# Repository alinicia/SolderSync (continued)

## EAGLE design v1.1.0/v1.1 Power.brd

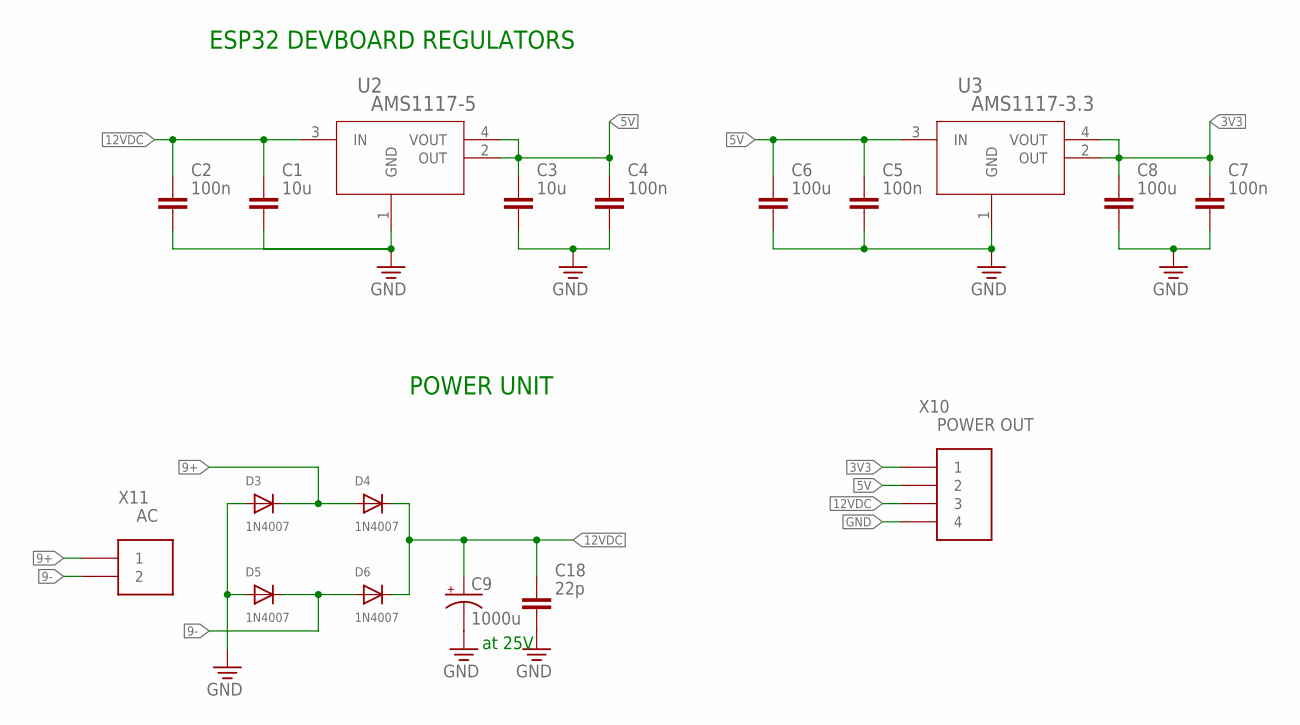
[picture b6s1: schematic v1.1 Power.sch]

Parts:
C1, C3: 10u; CAPC2012X110
C2, C4, C5, C7: 100n; CAPC2012X110
C6, C8: 100u; CAPC2012X110
C9: 1000u; CAP_10X20IN
C18: 22p; CAPC2012X110
D3, D4, D5, D6: 1N4007; SOD-123FL
U2: AMS1117-5; _AMS-L
U3: AMS1117-3.3; _ADS-L
X10: POWER OUT; JST-XH-04-PACKAGE-LONG-PAD
X11: AC; -LONG-PAD

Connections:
3V3: C7.1, C8.1, U3.2 (OUT), U3.4 (VOUT), X10.1
5V: C3.1, C4.1, C5.1, C6.1, U2.2 (OUT), U2.4 (VOUT), U3.3 (IN), X10.2
9+: D3.C, D4.A, X11.1
9-: D5.C, D6.A, X11.2
12VDC: C1.1, C2.1, C9.1 (+), C18.1, D4.C, D6.C, U2.3 (IN), X10.3
GND: C1.2, C2.2, C3.2, C4.2, C5.2, C6.2, C7.2, C8.2, C9.2 (-), C18.2, D3.A, D5.A, U2.1 (GND), U3.1 (GND), X10.4

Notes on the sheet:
ESP32 DEVBOARD REGULATORS
POWER UNIT
at 25V

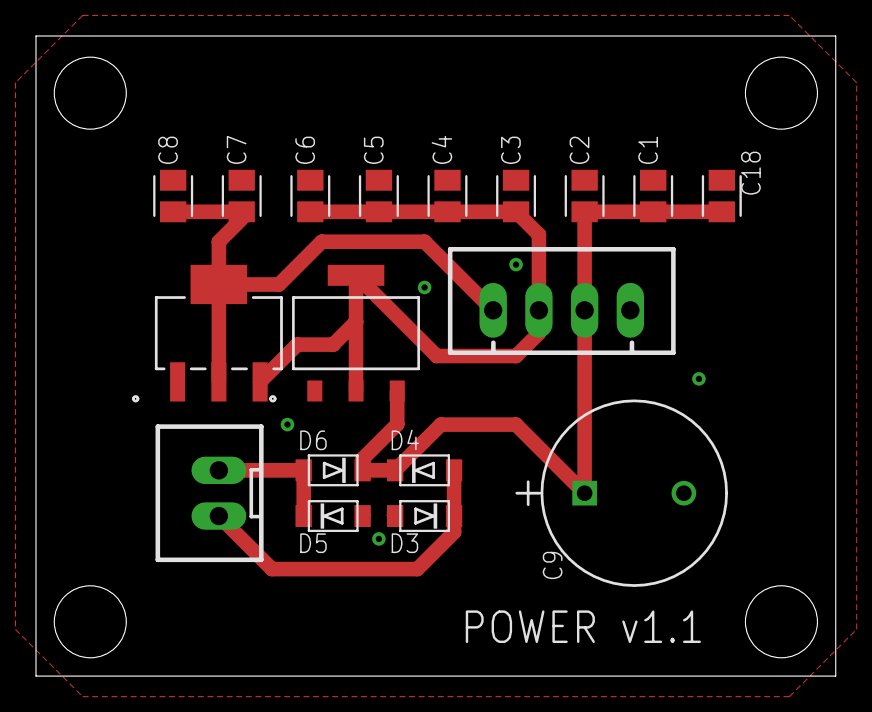
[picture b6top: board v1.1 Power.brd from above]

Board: 2 copper layers, 44.4 x 35.6 mm, 18 parts (0 on the bottom side), 6 nets.

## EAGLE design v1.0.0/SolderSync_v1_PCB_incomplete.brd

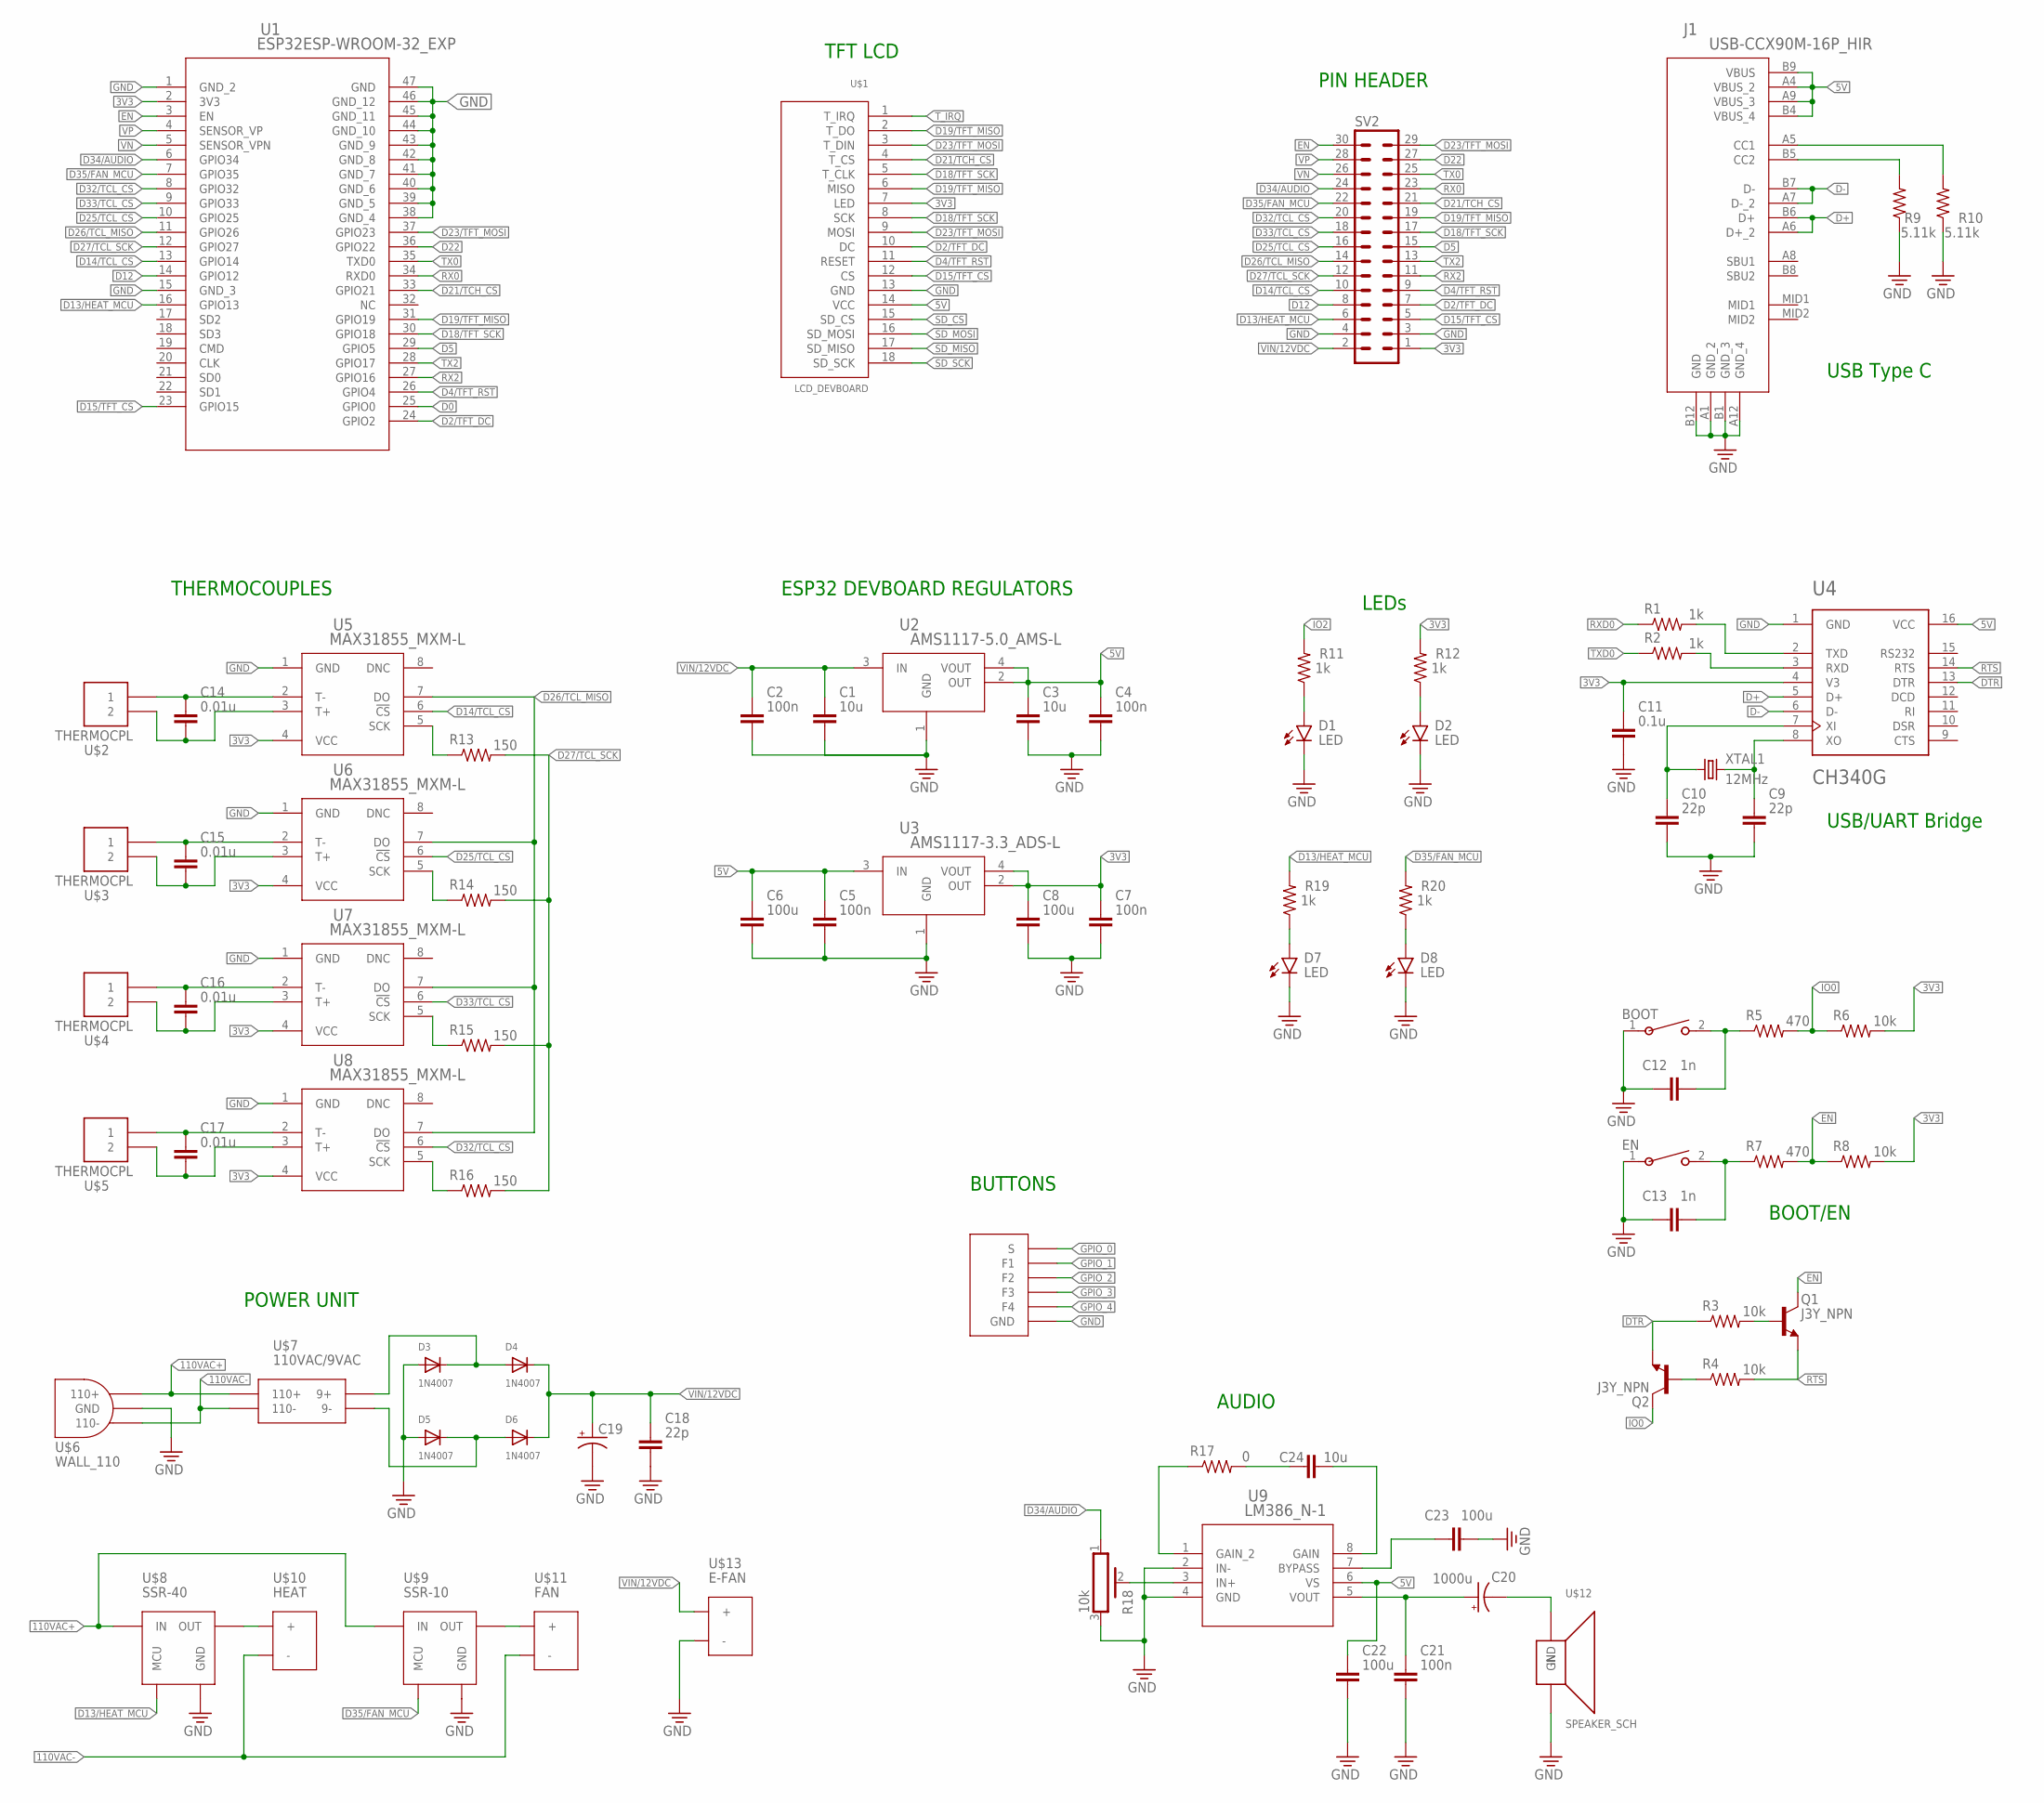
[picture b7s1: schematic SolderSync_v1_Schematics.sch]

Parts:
BOOT: EVQ22705RSW_EVQ22705R_PAN; SW_EVQ22705R_PAN
C1, C3, C24: 10u; CAPC2012X110
C2, C4, C5, C7, C21: 100n; CAPC2012X110
C6, C8, C22, C23: 100u; CAPC2012X110
C9, C10, C18: 22p; CAPC2012X110
C11: 0.1u; CAPC2012X110
C12, C13: 1n; CAPC2012X110
C14, C15, C16, C17: 0.01u; CAPC2012X110
C19: C-POL-US_ECAP-8.5MM; CAPAE830X1050N
C20: 1000u; CAPAE830X1050N
D1, D2, D7, D8: LED; LEDC2012X110N_FLAT-B
D3, D4, D5, D6: 1N4007; SOD-123FL
EN: EVQ22705RSW_EVQ22705R_PAN; SW_EVQ22705R_PAN
J1: USB-CCX90M-16P_HIR; USB-C
Q1, Q2: J3Y_NPN; SC59
R1, R2, R11, R12, R19, R20: 1k; RESC2012X65
R3, R4, R6, R8: 10k; RESC2012X65
R5, R7: 470; RESC2012X65
R9, R10: 5.11k; RESC2012X65
R13, R14, R15, R16: 150; RESC2012X65
R17: 0; RESC2012X65
R18: 10k; PV36W
SV2: 30-PIN
U1: ESP32ESP-WROOM-32_EXP; ESP32_SCH_PCB
U2: AMS1117-5.0_AMS-L; _AMS-L
U3: AMS1117-3.3_ADS-L; _ADS-L
U4: CH340G; SOIC127P600X180-16N
U5, U6, U7, U8: MAX31855_MXM-L; _MXM-L
U9: LM386_N-1; N08E_TEX
U$1: LCD_DEVBOARD; LCD_SCH
XTAL1: 12MHz; XTALRR488W45L1150T500H350B

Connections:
3V3: C7.1, C8.1, C11.1, R6.2, R8.2, R12.2, SV2.1, U1.2 (3V3), U3.2 (OUT), U3.4 (VOUT), U4.4 (V3), U5.4 (VCC), U6.4 (VCC), U7.4 (VCC), U8.4 (VCC), U$1.7 (LED)
5V: C3.1, C4.1, C5.1, C6.1, C22.1, J1.A4 (VBUS_2), J1.A9 (VBUS_3), J1.B4 (VBUS_4), J1.B9 (VBUS), U2.2 (OUT), U2.4 (VOUT), U3.3 (IN), U4.16 (VCC), U9.6 (VS), U$1.14 (VCC)
CC1: J1.A5 (CC1), R10.2
CC2: J1.B5 (CC2), R9.2
D0: U1.25 (GPIO0)
D2/TFT_DC: SV2.7, U1.24 (GPIO2), U$1.10 (DC)
D4/TFT_RST: SV2.9, U1.26 (GPIO4), U$1.11 (RESET)
D5: SV2.15, U1.29 (GPIO5)
D12: SV2.8, U1.14 (GPIO12)
D13/HEAT_MCU: R19.2, SV2.6, U1.16 (GPIO13)
D14/TCL_CS: SV2.10, U1.13 (GPIO14), U5.6 (!CS)
D15/TFT_CS: SV2.5, U1.23 (GPIO15), U$1.12 (CS)
D18/TFT_SCK: SV2.17, U1.30 (GPIO18), U$1.5 (T_CLK), U$1.8 (SCK)
D19/TFT_MISO: SV2.19, U1.31 (GPIO19), U$1.2 (T_DO), U$1.6 (MISO)
D21/TCH_CS: SV2.21, U1.33 (GPIO21), U$1.4 (T_CS)
D22: SV2.27, U1.36 (GPIO22)
D23/TFT_MOSI: SV2.29, U1.37 (GPIO23), U$1.3 (T_DIN), U$1.9 (MOSI)
D25/TCL_CS: SV2.16, U1.10 (GPIO25), U6.6 (!CS)
D26/TCL_MISO: SV2.14, U1.11 (GPIO26), U5.7 (DO), U6.7 (DO), U7.7 (DO), U8.7 (DO)
D27/TCL_SCK: R13.2, R14.2, R15.2, R16.2, SV2.12, U1.12 (GPIO27)
D32/TCL_CS: SV2.20, U1.8 (GPIO32), U8.6 (!CS)
D33/TCL_CS: SV2.18, U1.9 (GPIO33), U7.6 (!CS)
D34/AUDIO: R18.1, SV2.24, U1.6 (GPIO34)
D35/FAN_MCU: R20.2, SV2.22, U1.7 (GPIO35)
D+: J1.A6 (D+_2), J1.B6 (D+), U4.5 (D+)
D-: J1.A7 (D-_2), J1.B7 (D-), U4.6 (D-)
DTR: Q2.E, R3.1, U4.13 (DTR)
EN: Q1.C, R7.2, R8.1, SV2.30, U1.3 (EN)
GND: BOOT.1, C1.2, C2.2, C3.2, C4.2, C5.2, C6.2, C7.2, C8.2, C9.2, C10.2, C11.2, C12.1, C13.1, C18.2, C19.2 (-), C21.2, C22.2, C23.2, D1.C, D2.C, D3.A, D5.A, D7.C, D8.C, EN.1, J1.A1 (GND_2), J1.A12 (GND_4), J1.B1 (GND_3), J1.B12 (GND), R9.1, R10.1, R18.3, SV2.3, SV2.4, U1.1 (GND_2), U1.15 (GND_3), U1.38 (GND_4), U1.39 (GND_5), U1.40 (GND_6), U1.41 (GND_7), U1.42 (GND_8), U1.43 (GND_9), U1.44 (GND_10), U1.45 (GND_11), U1.46 (GND_12), U1.47 (GND), U2.1 (GND), U3.1 (GND), U4.1 (GND), U5.1 (GND), U6.1 (GND), U7.1 (GND), U8.1 (GND), U9.2 (IN-), U9.4 (GND), U$1.13 (GND)
IO0: Q2.C, R5.2, R6.1
IO2: R11.2
unnamed: D1.A, R11.1
unnamed: Q1.B, R3.2
unnamed: BOOT.2, C12.2, R5.1
unnamed: Q2.B, R4.1
unnamed: C14.2, U5.3 (T+)
unnamed: D2.A, R12.1
unnamed: D3.C, D4.A
unnamed: C13.2, EN.2, R7.1
unnamed: D5.C, D6.A
unnamed: C14.1, U5.2 (T-)
unnamed: C15.2, U6.3 (T+)
unnamed: C20.1 (+), C21.1, U9.5 (VOUT)
unnamed: C15.1, U6.2 (T-)
unnamed: C16.2, U7.3 (T+)
unnamed: C23.1, U9.7 (BYPASS)
unnamed: C16.1, U7.2 (T-)
unnamed: C17.2, U8.3 (T+)
unnamed: C24.1, R17.2
unnamed: C17.1, U8.2 (T-)
unnamed: R17.1, U9.1 (GAIN_2)
unnamed: C24.2, U9.8 (GAIN)
unnamed: R18.2, U9.3 (IN+)
unnamed: D7.A, R19.1
unnamed: D8.A, R20.1
RTS: Q1.E, R4.2, U4.14 (RTS)
RX0: SV2.23, U1.34 (RXD0)
RX2: SV2.11, U1.27 (GPIO16)
RXD: R2.2, U4.3 (RXD)
RXD0: R1.1
SD_CS: U$1.15 (SD_CS)
SD_MISO: U$1.17 (SD_MISO)
SD_MOSI: U$1.16 (SD_MOSI)
SD_SCK: U$1.18 (SD_SCK)
TCL_SCK1: R13.1, U5.5 (SCK)
TCL_SCK2: R14.1, U6.5 (SCK)
TCL_SCK3: R15.1, U7.5 (SCK)
TCL_SCK4: R16.1, U8.5 (SCK)
TX0: SV2.25, U1.35 (TXD0)
TX2: SV2.13, U1.28 (GPIO17)
TXD: R1.2, U4.2 (TXD)
TXD0: R2.1
T_IRQ: U$1.1 (T_IRQ)
VIN/12VDC: C1.1, C2.1, C18.1, C19.1 (+), D4.C, D6.C, SV2.2, U2.3 (IN)
VN: SV2.26, U1.5 (SENSOR_VPN)
VP: SV2.28, U1.4 (SENSOR_VP)
XO: C9.1, C10.1, U4.7 (XI), U4.8 (XO), XTAL1.1, XTAL1.2

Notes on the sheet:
ESP32 DEVBOARD REGULATORS
USB/UART Bridge
USB Type C
BOOT/EN
LEDs
THERMOCOUPLES
POWER UNIT
AUDIO
BUTTONS
TFT LCD
PIN HEADER

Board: 2 copper layers, 69 parts (0 on the bottom side), 68 nets, no tracks yet.

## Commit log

2024-11-28 Create file
2024-11-28 Rename Schematics_v1/AUDIO.png to v1.0.0/Schematics/AUDIO.png
2024-11-28 Rename Schematics_v1/BOOT_EN.png to v1.0.0/Schematics/BOOT_EN.png
2024-11-28 Rename Schematics_v1/BUTTONS.png to v1.0.0/Schematics/BUTTONS.png
2024-11-28 Rename Schematics_v1/ESP32.png to v1.0.0/Schematics/ESP32.png
2024-11-28 Rename Schematics_v1/Full Schematics_v1.rar to v1.0.0/Schematics/Full Schematics_v1.rar
2024-11-28 Rename Schematics_v1/LCD.png to v1.0.0/Schematics/LCD.png
2024-11-28 Rename Schematics_v1/LEDs.png to v1.0.0/Schematics/LEDs.png
2024-11-28 Rename Schematics_v1/PIN HEADER.png to v1.0.0/Schematics/PIN HEADER.png
2024-11-28 Rename Schematics_v1/POWER_UNIT_HEAT_FAN.png to v1.0.0/Schematics/POWER_UNIT_HEAT_FAN.png
2024-11-28 Rename Schematics_v1/THERMOCOUPLES.png to v1.0.0/Schematics/THERMOCOUPLES.png
2024-11-28 Rename Schematics_v1/USB-C.png to v1.0.0/Schematics/USB-C.png
2024-11-28 Rename Schematics_v1/USB_UART_BRIDGE.png to v1.0.0/Schematics/USB_UART_BRIDGE.png
2024-11-28 Rename Schematics_v1/VOLTAGE REGULATORS.png to v1.0.0/Schematics/VOLTAGE REGULATORS.png
2025-04-16 Create f
2025-04-16 Rename v1.0.0/Schematics/AUDIO.png to v1.0.0/Schematics/Main/AUDIO.png
2025-04-16 Rename v1.0.0/Schematics/BOOT_EN.png to v1.0.0/Schematics/Main/BOOT_EN.png
2025-04-16 Rename v1.0.0/Schematics/BUTTONS.png to v1.0.0/Schematics/Main/BUTTONS.png
2025-04-16 Rename v1.0.0/Schematics/ESP32.png to v1.0.0/Schematics/Main/ESP32.png
2025-04-17 move
2025-04-17 v2.0
2025-04-17 2.1 update
2025-04-17 2.1 add
